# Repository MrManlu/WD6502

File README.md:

# WD6502
Prototyping SBC based on W65C02 CPU

## Why?
This is a minimal CPU<->RAM<->ROM interconnection to achieve a fast breadboard prototyping, minimizing bad connections occurred when connecting several jumper wires.

There is no fixed memory map. Freedom for everyone! There exists a half-sized breadboard in the upper-right zone of the PCB to create the address decoding circuit. Also, there exists a lower full-sized breadboard to connect peripherals: VIAs, ACIAs, SD card breakout boards,... 

## Contributing
This project is in its first steps. Feel free to contibute/fork as you want. **I'm a newbie in HW design, so please do constructive criticism!**

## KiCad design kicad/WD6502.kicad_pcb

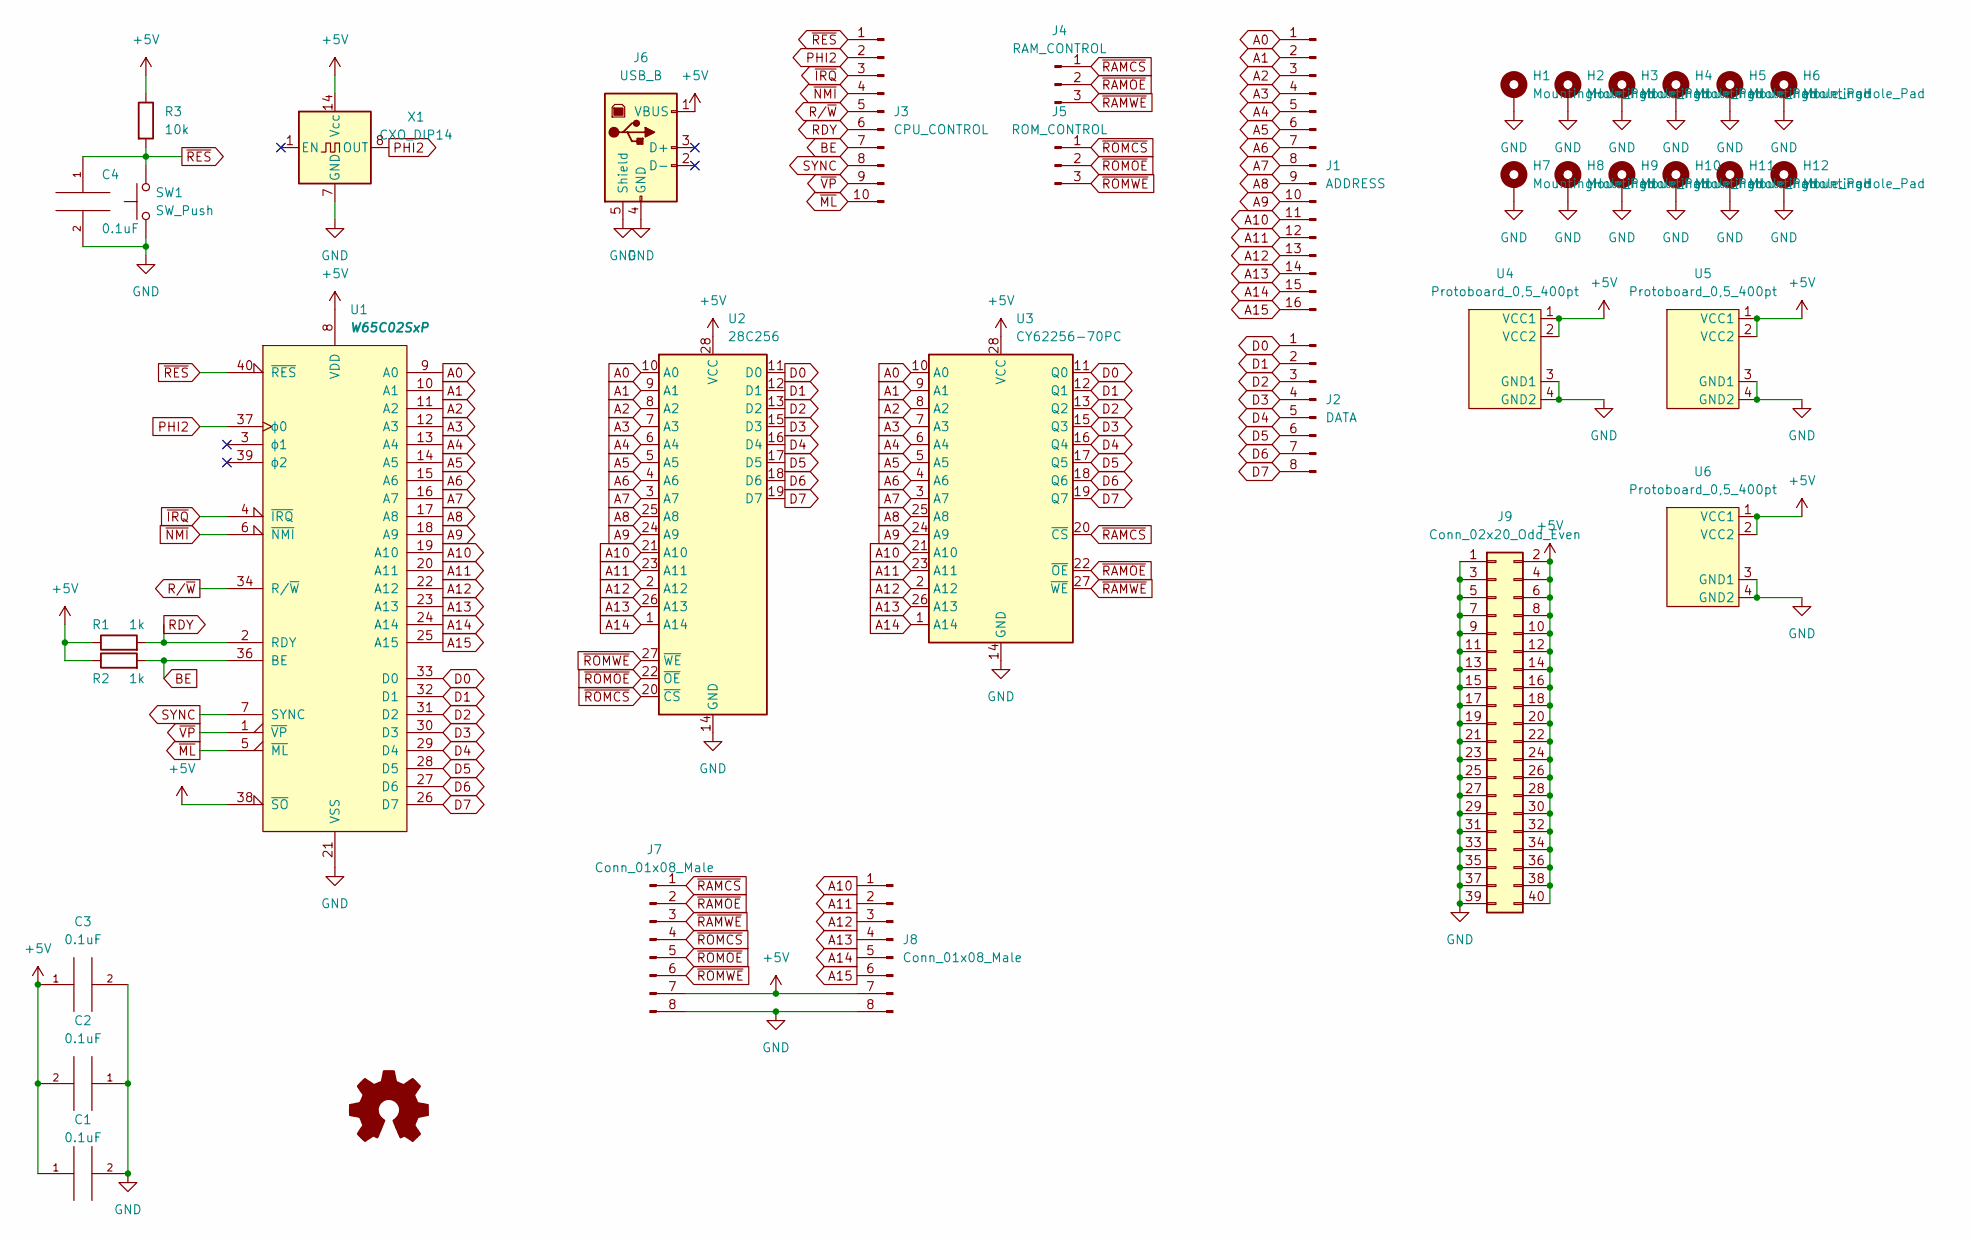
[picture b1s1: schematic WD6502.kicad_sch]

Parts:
C1, C2, C3, C4: 0.1uF; C_Disc_D5.0mm_W2.5mm_P2.50mm
H1, H2, H3, H4, H5, H6, H7, H8, H9, H10, H11, H12: MountingHole_Pad; MountingHole_3.2mm_M3_Pad_Via
J1: ADDRESS; PinSocket_1x16_P2.54mm_Vertical
J2: DATA; PinSocket_1x08_P2.54mm_Vertical
J3: CPU_CONTROL; PinSocket_1x10_P2.54mm_Vertical
J4: RAM_CONTROL; PinSocket_1x03_P2.54mm_Vertical
J5: ROM_CONTROL; PinSocket_1x03_P2.54mm_Vertical
J6: USB_B; USB_B_Lumberg_2411_02_Horizontal
J7, J8: Conn_01x08_Male; PinSocket_1x08_P2.54mm_Vertical
J9: Conn_02x20_Odd_Even; PinSocket_2x20_P2.54mm_Vertical
R1, R2: 1k; R_Axial_DIN0309_L9.0mm_D3.2mm_P12.70mm_Horizontal
R3: 10k; R_Axial_DIN0309_L9.0mm_D3.2mm_P12.70mm_Horizontal
SW1: SW_Push; SW_PUSH_6mm
U1: W65C02SxP; DIP-40_W15.24mm_Socket_LongPads
U2: 28C256; DIP-28_W15.24mm_Socket_LongPads
U3: CY62256-70PC; DIP-28_W15.24mm_Socket_LongPads
U4, U5, U6: Protoboard_0,5_400pt; Protoboard_Perfboard_0,5_400pt
X1: CXO_DIP14; Oscillator_DIP-14

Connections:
+5V: C1.1, C2.2, C3.1, J6.1 (VBUS), J7.7, J8.7, J9.2, J9.4, J9.6, J9.8, J9.10, J9.12, J9.14, J9.16, J9.18, J9.20, J9.22, J9.24, J9.26, J9.28, J9.30, J9.32, J9.34, J9.36, J9.38, J9.40, R1.1, R2.1, R3.1, U1.8 (VDD), U1.38 (~SO), U2.28 (VCC), U3.28 (VCC), U4.1 (VCC1), U4.2 (VCC2), U5.1 (VCC1), U5.2 (VCC2), U6.1 (VCC1), U6.2 (VCC2), X1.14 (Vcc)
A0: J1.1, U1.9 (A0), U2.10 (A0), U3.10 (A0)
A1: J1.2, U1.10 (A1), U2.9 (A1), U3.9 (A1)
A2: J1.3, U1.11 (A2), U2.8 (A2), U3.8 (A2)
A3: J1.4, U1.12 (A3), U2.7 (A3), U3.7 (A3)
A4: J1.5, U1.13 (A4), U2.6 (A4), U3.6 (A4)
A5: J1.6, U1.14 (A5), U2.5 (A5), U3.5 (A5)
A6: J1.7, U1.15 (A6), U2.4 (A6), U3.4 (A6)
A7: J1.8, U1.16 (A7), U2.3 (A7), U3.3 (A7)
A8: J1.9, U1.17 (A8), U2.25 (A8), U3.25 (A8)
A9: J1.10, U1.18 (A9), U2.24 (A9), U3.24 (A9)
A10: J1.11, J8.1, U1.19 (A10), U2.21 (A10), U3.21 (A10)
A11: J1.12, J8.2, U1.20 (A11), U2.23 (A11), U3.23 (A11)
A12: J1.13, J8.3, U1.22 (A12), U2.2 (A12), U3.2 (A12)
A13: J1.14, J8.4, U1.23 (A13), U2.26 (A13), U3.26 (A13)
A14: J1.15, J8.5, U1.24 (A14), U2.1 (A14), U3.1 (A14)
A15: J1.16, J8.6, U1.25 (A15)
BE: J3.7, R2.2, U1.36 (BE)
D0: J2.1, U1.33 (D0), U2.11 (D0), U3.11 (Q0)
D1: J2.2, U1.32 (D1), U2.12 (D1), U3.12 (Q1)
D2: J2.3, U1.31 (D2), U2.13 (D2), U3.13 (Q2)
D3: J2.4, U1.30 (D3), U2.15 (D3), U3.15 (Q3)
D4: J2.5, U1.29 (D4), U2.16 (D4), U3.16 (Q4)
D5: J2.6, U1.28 (D5), U2.17 (D5), U3.17 (Q5)
D6: J2.7, U1.27 (D6), U2.18 (D6), U3.18 (Q6)
D7: J2.8, U1.26 (D7), U2.19 (D7), U3.19 (Q7)
GND: C1.2, C2.1, C3.2, C4.2, H1.1, H2.1, H3.1, H4.1, H5.1, H6.1, H7.1, H8.1, H9.1, H10.1, H11.1, H12.1, J6.4 (GND), J6.5 (Shield), J7.8, J8.8, J9.1, J9.3, J9.5, J9.7, J9.9, J9.11, J9.13, J9.15, J9.17, J9.19, J9.21, J9.23, J9.25, J9.27, J9.29, J9.31, J9.33, J9.35, J9.37, J9.39, SW1.1, U1.21 (VSS), U2.14 (GND), U3.14 (GND), U4.3 (GND1), U4.4 (GND2), U5.3 (GND1), U5.4 (GND2), U6.3 (GND1), U6.4 (GND2), X1.7 (GND)
PHI2: J3.2, U1.37 (ϕ0), X1.8 (OUT)
RDY: J3.6, R1.2, U1.2 (RDY)
R/~W: J3.5, U1.34 (R/~W)
SYNC: J3.8, U1.7 (SYNC)
~IRQ: J3.3, U1.4 (~IRQ)
~ML: J3.10, U1.5 (~ML)
~NMI: J3.4, U1.6 (~NMI)
~RAMCS: J4.1, J7.1, U3.20 (~CS)
~RAMOE: J4.2, J7.2, U3.22 (~OE)
~RAMWE: J4.3, J7.3, U3.27 (~WE)
~RES: C4.1, J3.1, R3.2, SW1.2, U1.40 (~RES)
~ROMCS: J5.1, J7.4, U2.20 (~CS)
~ROMOE: J5.2, J7.5, U2.22 (~OE)
~ROMWE: J5.3, J7.6, U2.27 (~WE)
~VP: J3.9, U1.1 (~VP)

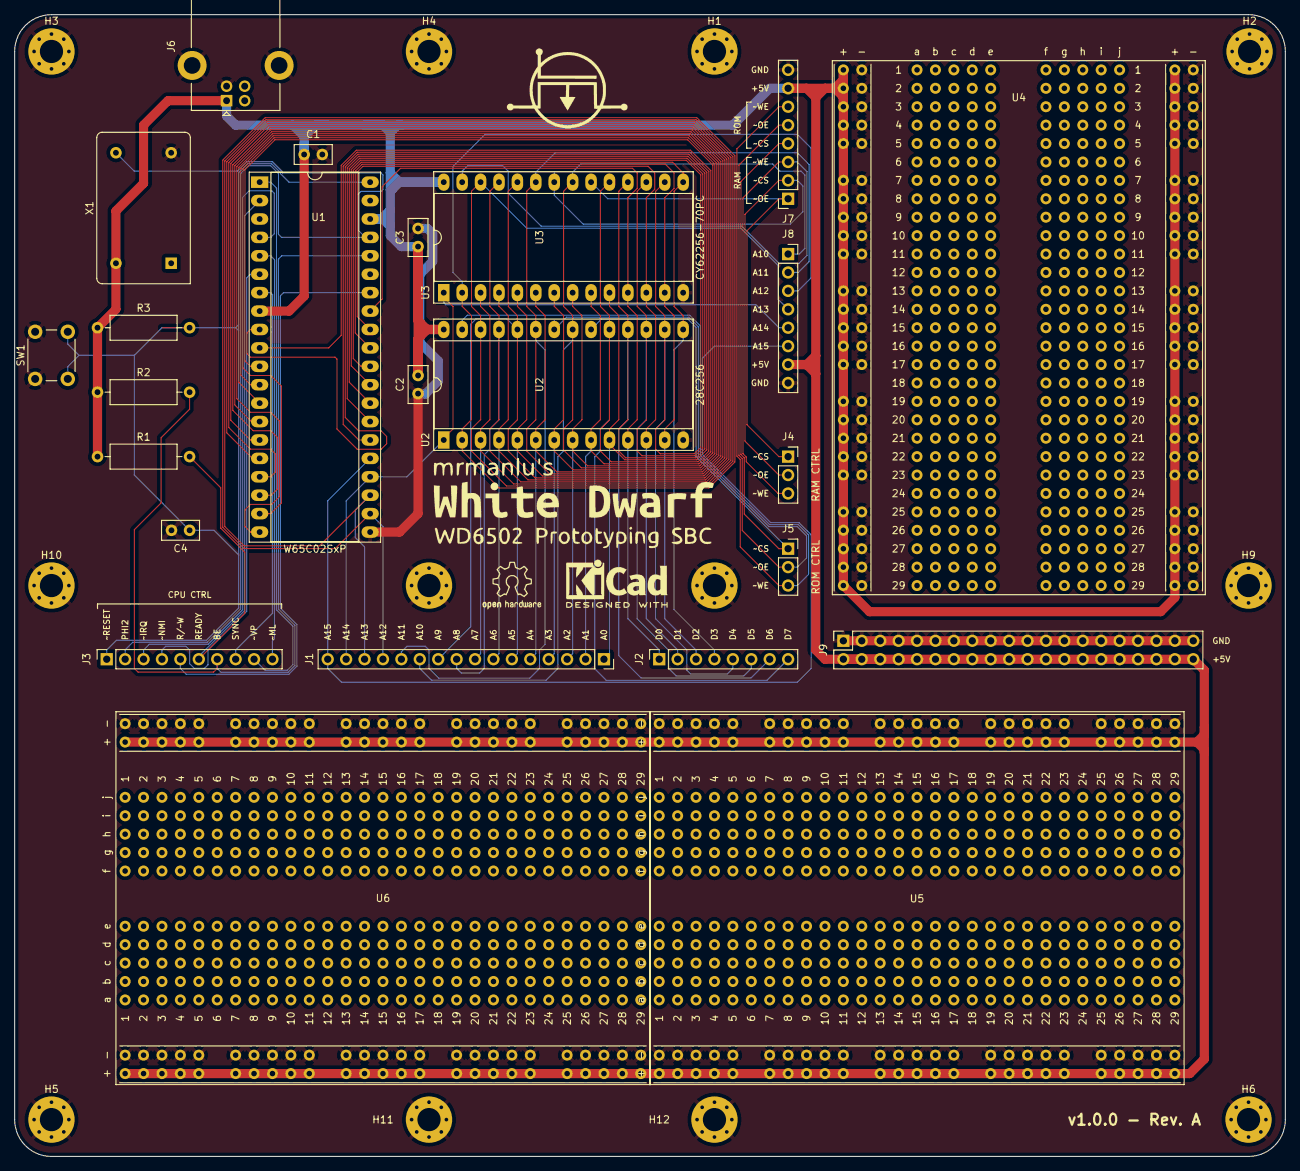
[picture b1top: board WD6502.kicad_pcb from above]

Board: 2 copper layers, 175.3 x 157.5 mm, 36 parts (0 on the bottom side), 42 nets.

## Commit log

2022-11-18 Added source files
